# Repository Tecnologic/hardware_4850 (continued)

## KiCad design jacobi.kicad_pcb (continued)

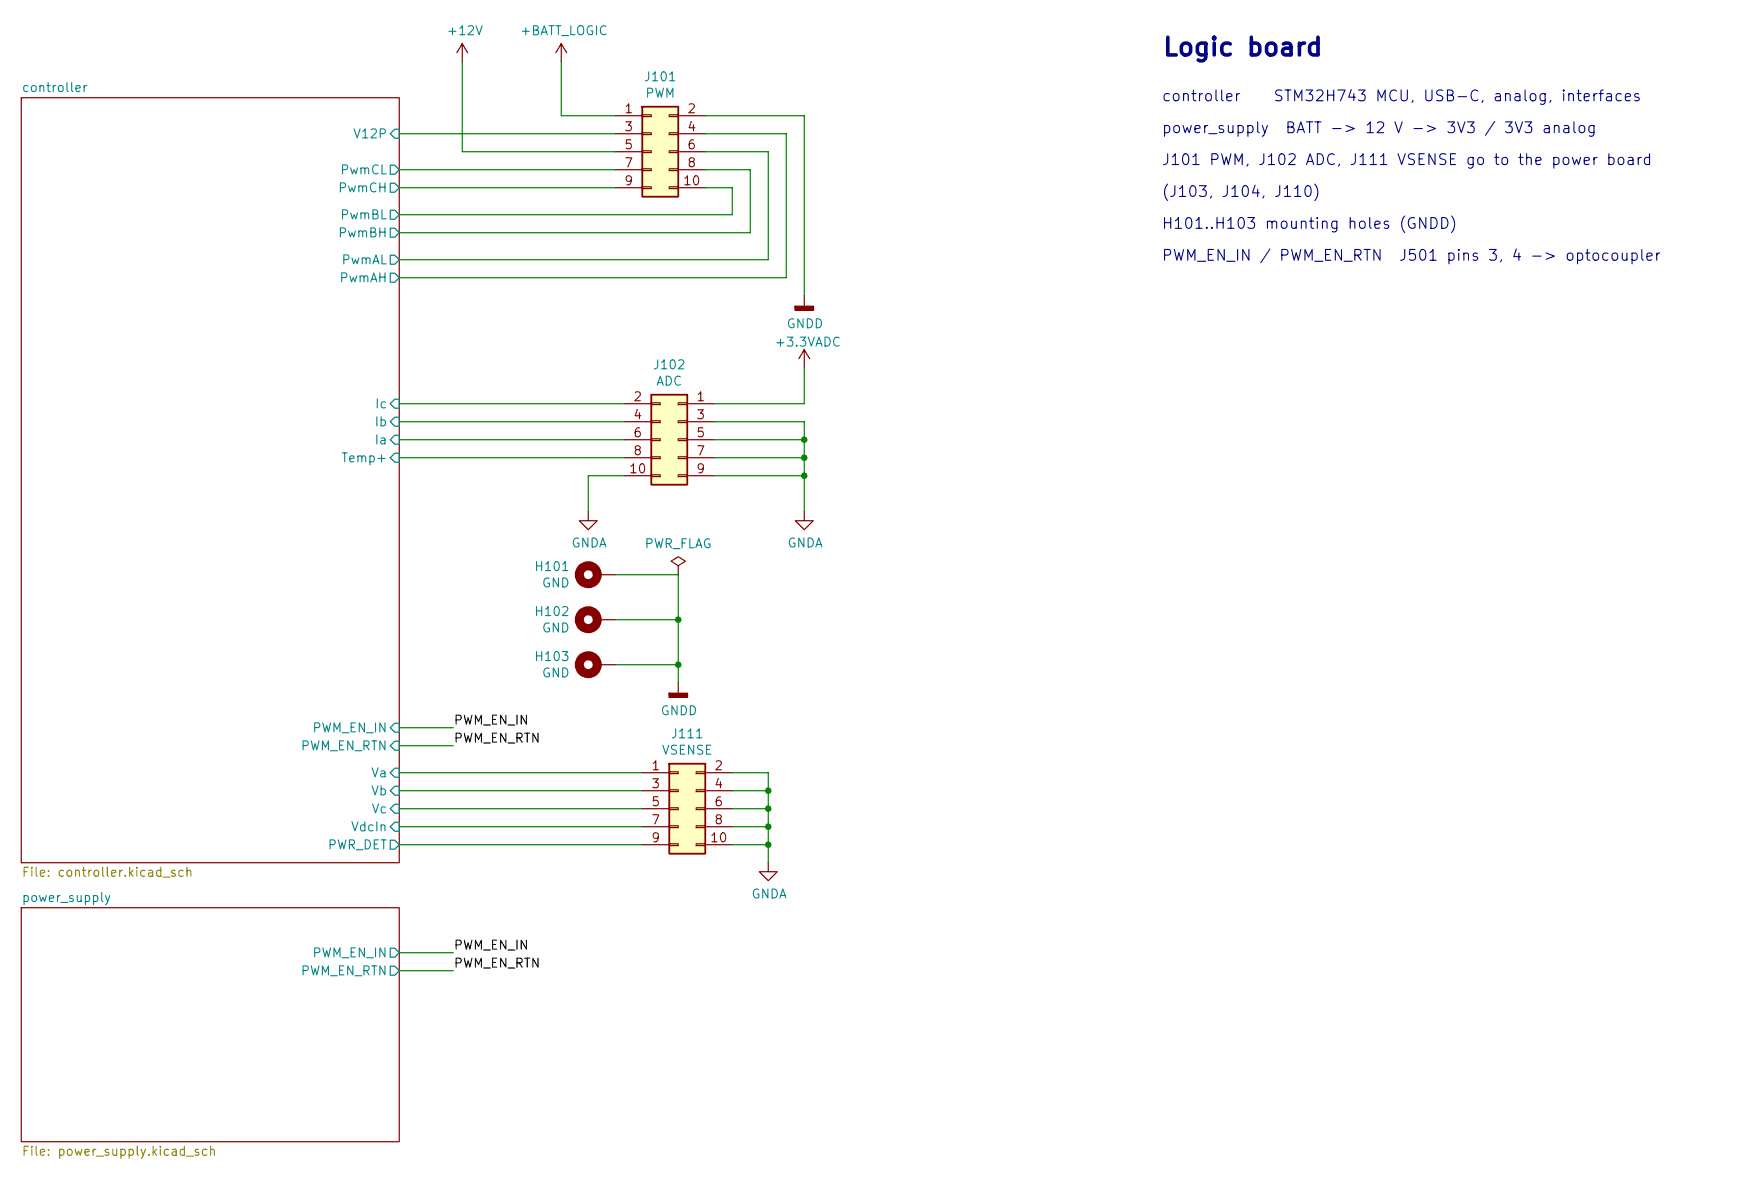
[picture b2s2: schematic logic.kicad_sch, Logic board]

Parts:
H101: GND; MountingHole_3.2mm_M3_Pad_Via
H102, H103: GND; MountingHole_3.2mm_M3_ISO14580_Pad
J101: PWM; PinHeader_2x05_P2.54mm_Vertical_SMD; Part# C124391
J102: ADC; PinHeader_2x05_P2.54mm_Vertical_SMD; Part# C124391
J111: VSENSE; PinHeader_2x05_P2.54mm_Vertical_SMD; Part# C124391

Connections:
+3.3VADC: J102.1; also elsewhere on the board
+12V: J101.5; also elsewhere on the board
+BATT_LOGIC: J101.1; also elsewhere on the board
/logic/controller/Ia: J102.6; also elsewhere on the board
/logic/controller/Ib: J102.4; also elsewhere on the board
/logic/controller/Ic: J102.2; also elsewhere on the board
/logic/controller/PWR_DET: J111.9; also elsewhere on the board
/logic/controller/PwmAH: J101.4; also elsewhere on the board
/logic/controller/PwmAL: J101.6; also elsewhere on the board
/logic/controller/PwmBH: J101.8; also elsewhere on the board
/logic/controller/PwmBL: J101.10; also elsewhere on the board
/logic/controller/PwmCH: J101.9; also elsewhere on the board
/logic/controller/PwmCL: J101.7; also elsewhere on the board
/logic/controller/Temp+: J102.8; also elsewhere on the board
/logic/controller/V12P: J101.3; also elsewhere on the board
/logic/controller/Va: J111.1; also elsewhere on the board
/logic/controller/Vb: J111.3; also elsewhere on the board
/logic/controller/Vc: J111.5; also elsewhere on the board
/logic/controller/VdcIn: J111.7; also elsewhere on the board
GNDA: J102.3, J102.5, J102.7, J102.9, J102.10, J111.2, J111.4, J111.6, J111.8, J111.10; also elsewhere on the board
GNDD: H101.1 (1_1), H102.1 (1_1), H103.1 (1_1), J101.2; also elsewhere on the board

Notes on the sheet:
power_supply BATT -> 12 V -> 3V3 / 3V3 analog
PWM_EN_IN / PWM_EN_RTN J501 pins 3, 4 -> optocoupler
(J103, J104, J110)
Logic board
J101 PWM, J102 ADC, J111 VSENSE go to the power board
controller STM32H743 MCU, USB-C, analog, interfaces
H101..H103 mounting holes (GNDD)

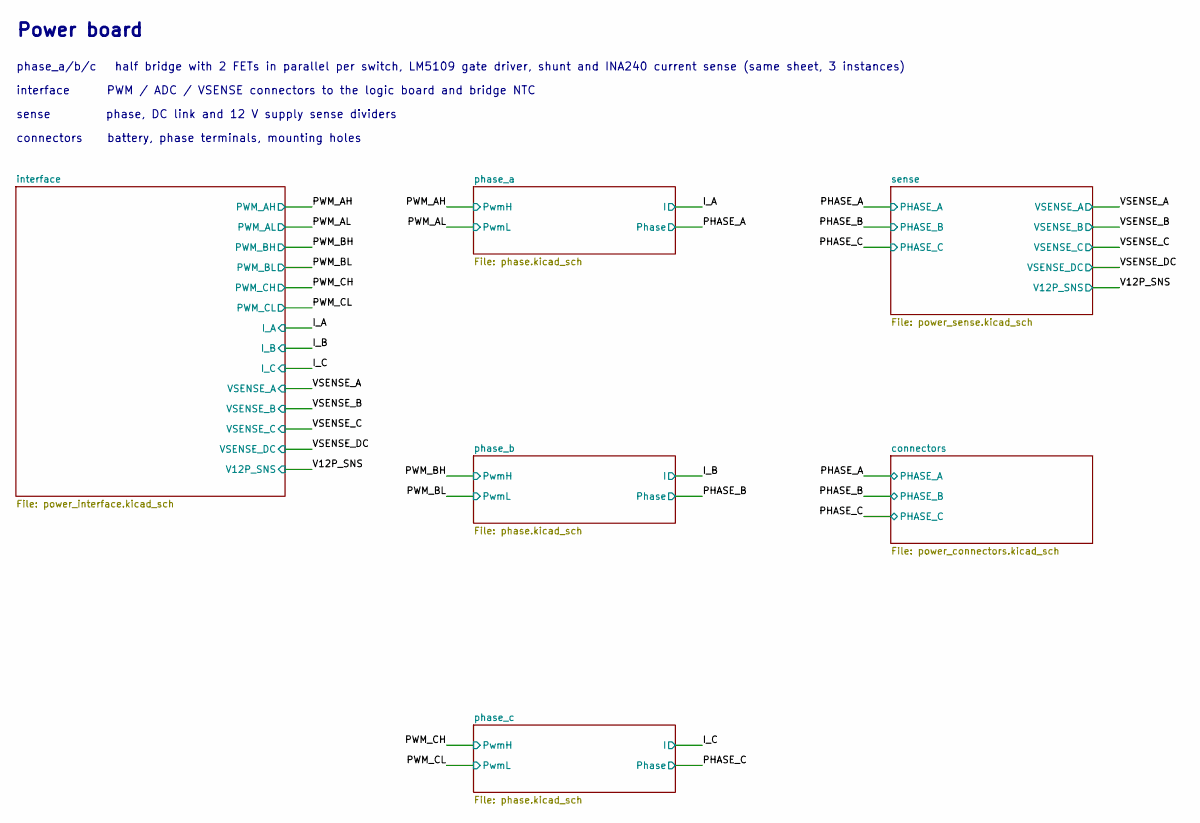
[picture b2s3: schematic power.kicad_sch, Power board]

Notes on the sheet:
phase_a/b/c half bridge with 2 FETs in parallel per switch, LM5109 gate driver, shunt and INA240 current sense (same sheet, 3 instances)
Power board
interface PWM / ADC / VSENSE connectors to the logic board and bridge NTC
sense phase, DC link and 12 V supply sense dividers
connectors battery, phase terminals, mounting holes

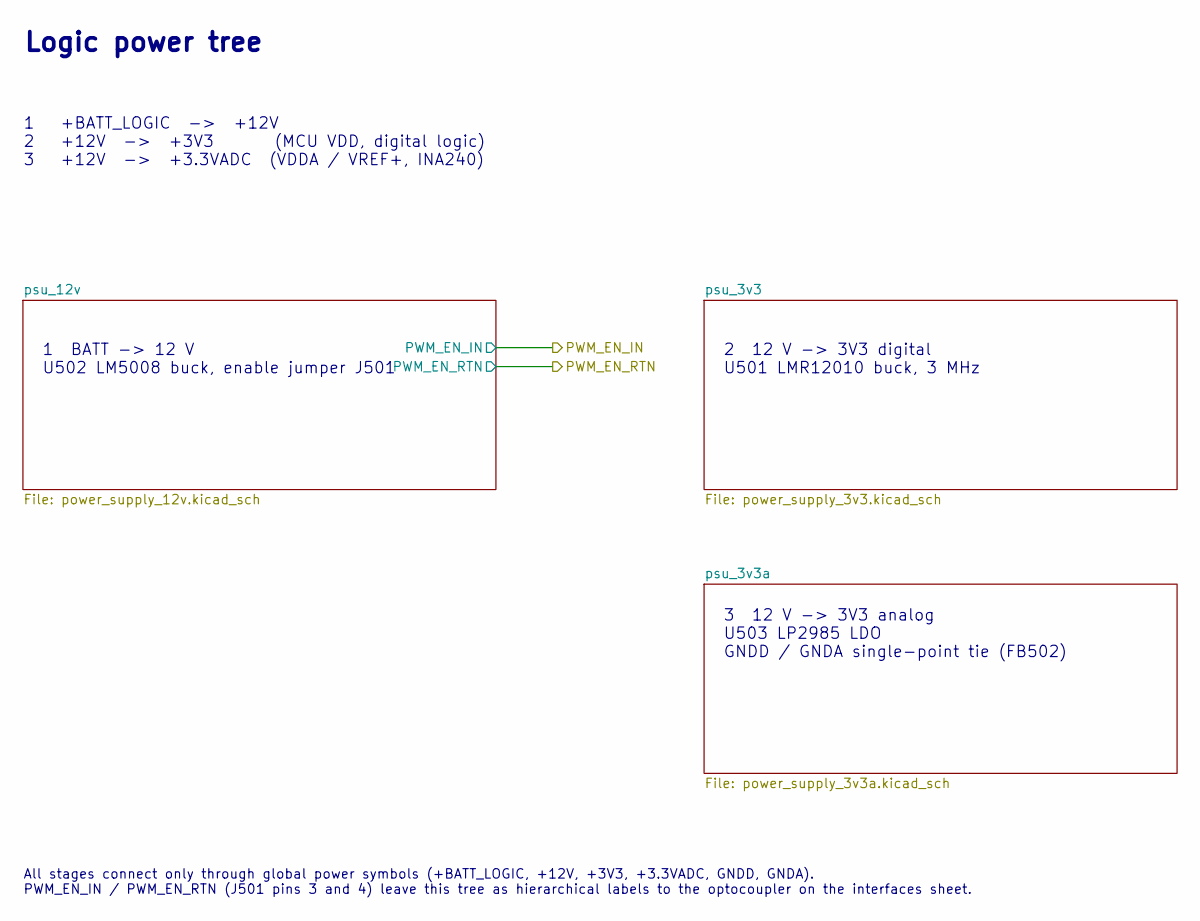
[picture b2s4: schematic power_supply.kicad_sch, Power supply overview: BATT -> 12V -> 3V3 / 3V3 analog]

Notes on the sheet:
All stages connect only through global power symbols (+BATT_LOGIC, +12V, +3V3, +3.3VADC, GNDD, GNDA). PWM_EN_IN / PWM_EN_RTN (J501 pins 3 and 4) leave this tree as hierarchical labels to the optocoupler on the interfaces sheet.
2 12 V -> 3V3 digital U501 LMR12010 buck, 3 MHz
3 12 V -> 3V3 analog U503 LP2985 LDO GNDD / GNDA single-point tie (FB502)
1 +BATT_LOGIC -> +12V 2 +12V -> +3V3 (MCU VDD, digital logic) 3 +12V -> +3.3VADC (VDDA / VREF+, INA240)
1 BATT -> 12 V U502 LM5008 buck, enable jumper J501
Logic power tree

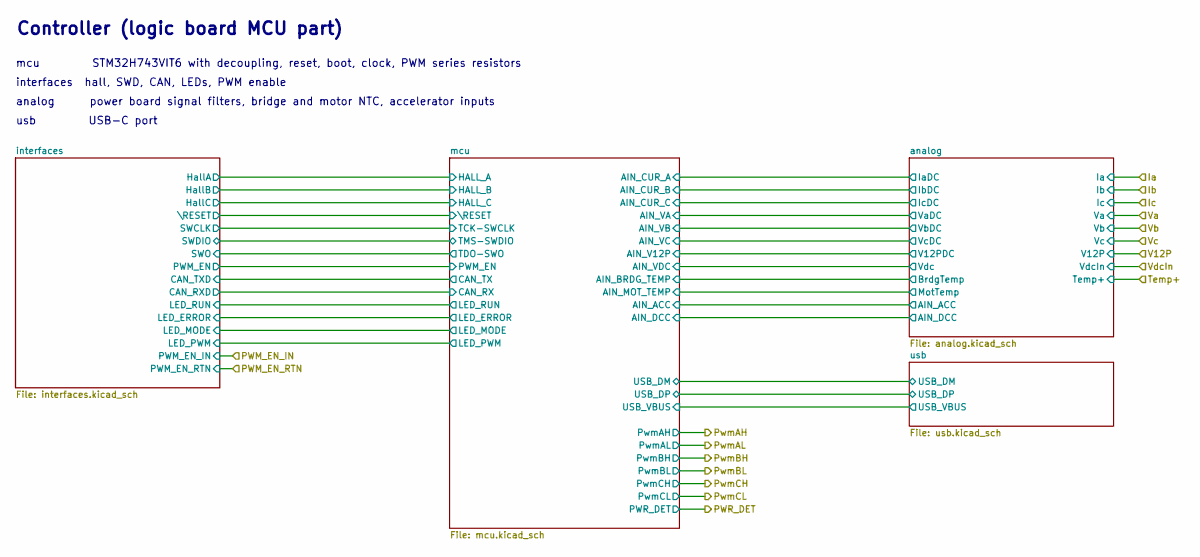
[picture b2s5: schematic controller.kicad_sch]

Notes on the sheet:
usb USB-C port
Controller (logic board MCU part)
mcu STM32H743VIT6 with decoupling, reset, boot, clock, PWM series resistors
interfaces hall, SWD, CAN, LEDs, PWM enable
analog power board signal filters, bridge and motor NTC, accelerator inputs

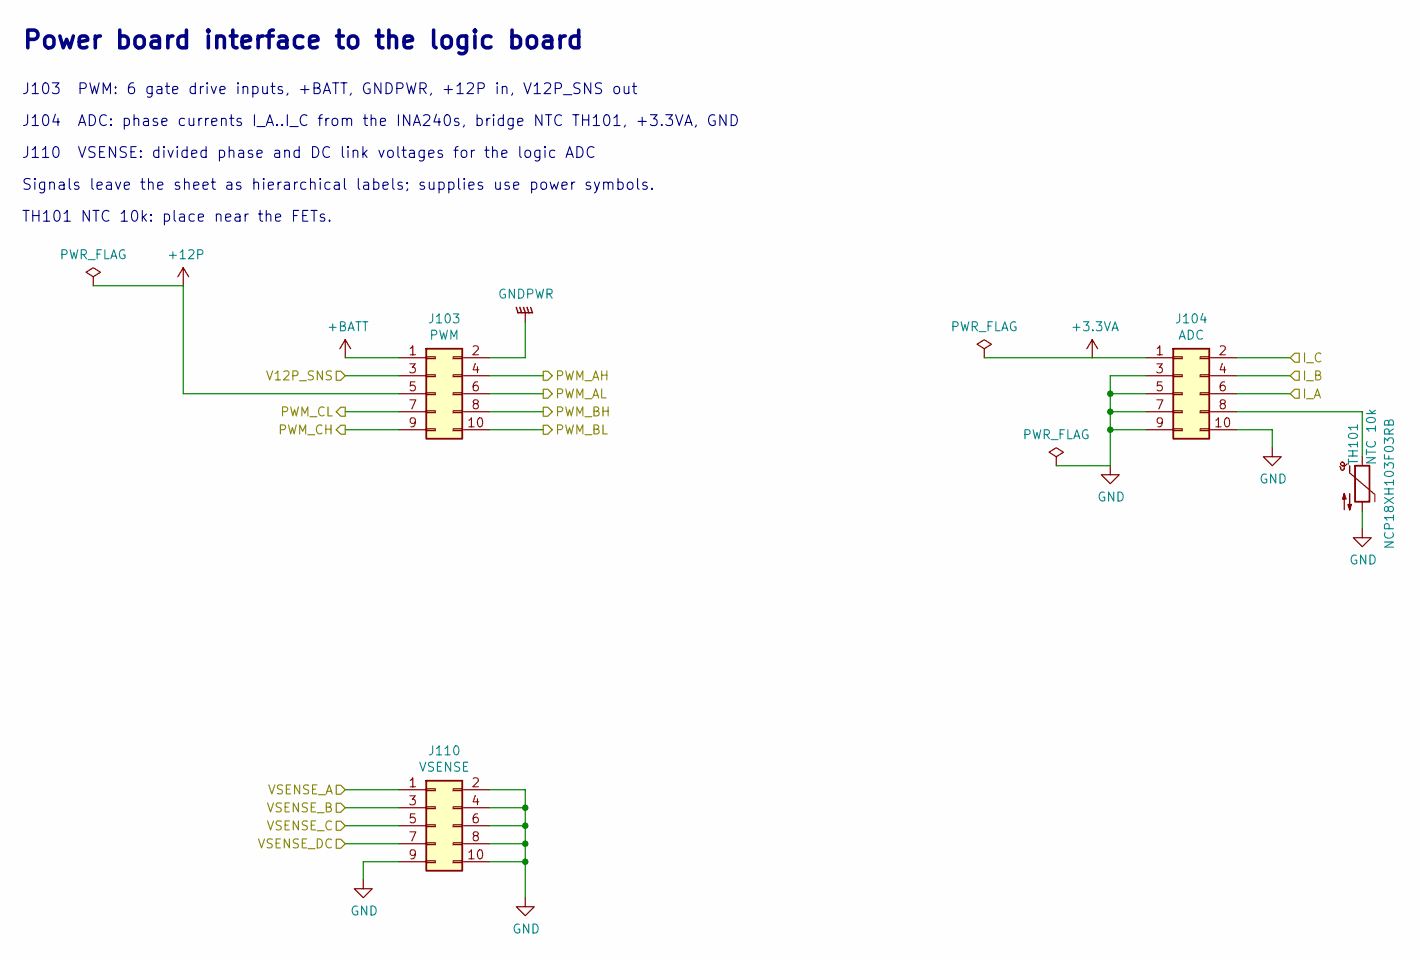
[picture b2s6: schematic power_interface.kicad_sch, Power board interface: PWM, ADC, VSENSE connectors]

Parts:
J103: PWM; PinSocket_2x05_P2.54mm_Vertical_SMD; Part# C261072
J104: ADC; PinSocket_2x05_P2.54mm_Vertical_SMD; Part# C261072
J110: VSENSE; PinSocket_2x05_P2.54mm_Vertical_SMD; Part# C261072
TH101: NTC 10k; R_0603_1608Metric; Part# NCP18XH103F03RB

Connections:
+3.3VA: J104.1; also elsewhere on the board
+12P: J103.5; also elsewhere on the board
+BATT: J103.1; also elsewhere on the board
/power/I_A: J104.6; also elsewhere on the board
/power/I_B: J104.4; also elsewhere on the board
/power/I_C: J104.2; also elsewhere on the board
/power/PWM_AH: J103.4; also elsewhere on the board
/power/PWM_AL: J103.6; also elsewhere on the board
/power/PWM_BH: J103.8; also elsewhere on the board
/power/PWM_BL: J103.10; also elsewhere on the board
/power/PWM_CH: J103.9; also elsewhere on the board
/power/PWM_CL: J103.7; also elsewhere on the board
/power/V12P_SNS: J103.3; also elsewhere on the board
/power/VSENSE_A: J110.1; also elsewhere on the board
/power/VSENSE_B: J110.3; also elsewhere on the board
/power/VSENSE_C: J110.5; also elsewhere on the board
/power/VSENSE_DC: J110.7; also elsewhere on the board
GND: J104.3, J104.5, J104.7, J104.9, J104.10, J110.2, J110.4, J110.6, J110.8, J110.9, J110.10, TH101.2; also elsewhere on the board
GNDPWR: J103.2; also elsewhere on the board
unnamed: J104.8, TH101.1

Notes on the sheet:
J110 VSENSE: divided phase and DC link voltages for the logic ADC
TH101 NTC 10k: place near the FETs.
J103 PWM: 6 gate drive inputs, +BATT, GNDPWR, +12P in, V12P_SNS out
Signals leave the sheet as hierarchical labels; supplies use power symbols.
Power board interface to the logic board
J104 ADC: phase currents I_A..I_C from the INA240s, bridge NTC TH101, +3.3VA, GND

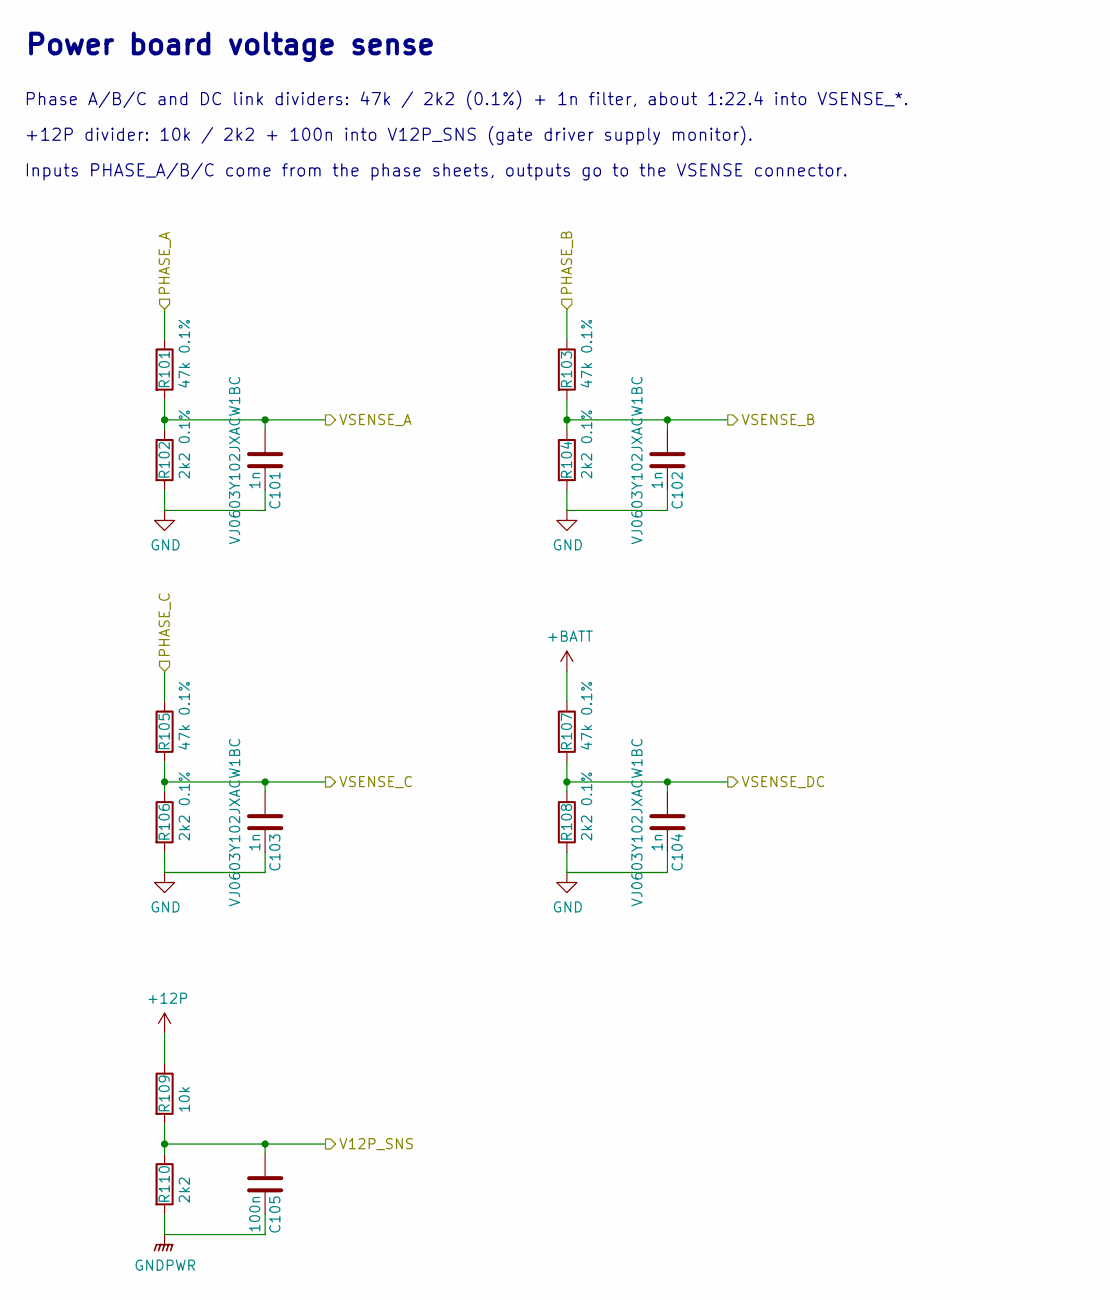
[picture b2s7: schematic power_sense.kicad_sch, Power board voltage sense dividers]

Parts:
C101, C102, C103, C104: 1n; C_0603_1608Metric; Part# VJ0603Y102JXACW1BC
C105: 100n; C_0603_1608Metric
R101, R103, R105, R107: 47k 0.1%; R_0805_2012Metric
R102, R104, R106, R108: 2k2 0.1%; R_0603_1608Metric
R109: 10k; R_0603_1608Metric
R110: 2k2; R_0603_1608Metric

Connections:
+12P: R109.1; also elsewhere on the board
+BATT: R107.1; also elsewhere on the board
/power/PHASE_A: R101.1; also elsewhere on the board
/power/PHASE_B: R103.1; also elsewhere on the board
/power/PHASE_C: R105.1; also elsewhere on the board
/power/V12P_SNS: C105.2, R109.2, R110.1; also elsewhere on the board
/power/VSENSE_A: C101.2, R101.2, R102.1; also elsewhere on the board
/power/VSENSE_B: C102.2, R103.2, R104.1; also elsewhere on the board
/power/VSENSE_C: C103.2, R105.2, R106.1; also elsewhere on the board
/power/VSENSE_DC: C104.2, R107.2, R108.1; also elsewhere on the board
GND: C101.1, C102.1, C103.1, C104.1, R102.2, R104.2, R106.2, R108.2; also elsewhere on the board
GNDPWR: C105.1, R110.2; also elsewhere on the board

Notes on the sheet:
Inputs PHASE_A/B/C come from the phase sheets, outputs go to the VSENSE connector.
+12P divider: 10k / 2k2 + 100n into V12P_SNS (gate driver supply monitor).
Power board voltage sense
Phase A/B/C and DC link dividers: 47k / 2k2 (0.1%) + 1n filter, about 1:22.4 into VSENSE_*.

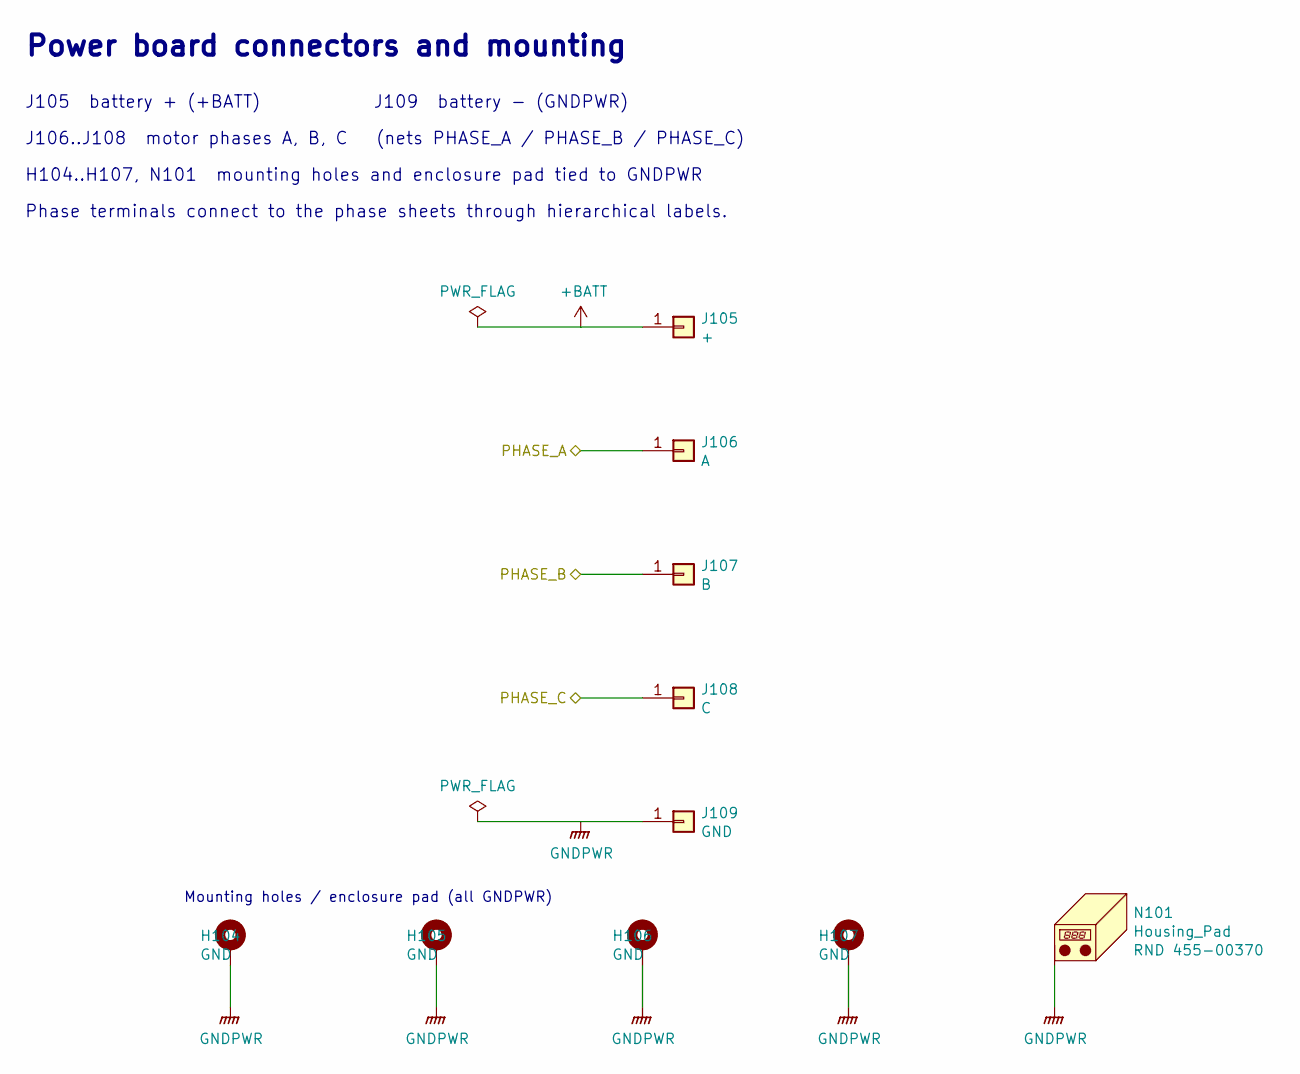
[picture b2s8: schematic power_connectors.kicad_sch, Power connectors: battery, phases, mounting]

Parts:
H104, H107: GND; MountingHole_3.2mm_M3_ISO14580_Pad
H105, H106: GND; MountingHole_3.2mm_M3_Pad_Via
J105: +; Terminal_M3_XFCN_TT34086077-0910; LCSC C19724597
J106: A; Terminal_M3_XFCN_TT34086077-0910; LCSC C19724597
J107: B; Terminal_M3_XFCN_TT34086077-0910; LCSC C19724597
J108: C; Terminal_M3_XFCN_TT34086077-0910; LCSC C19724597
J109: GND; Terminal_M3_XFCN_TT34086077-0910; LCSC C19724597
N101: Housing_Pad; RND-455-00370; Part# RND 455-00370

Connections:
+BATT: J105.1 (Pin_1_1); also elsewhere on the board
/power/PHASE_A: J106.1 (Pin_1_1); also elsewhere on the board
/power/PHASE_B: J107.1 (Pin_1_1); also elsewhere on the board
/power/PHASE_C: J108.1 (Pin_1_1); also elsewhere on the board
GNDPWR: H104.1 (1_1), H105.1 (1_1), H106.1 (1_1), H107.1 (1_1), J109.1 (Pin_1_1), N101.1 (PAD_1); also elsewhere on the board

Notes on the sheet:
J106..J108 motor phases A, B, C (nets PHASE_A / PHASE_B / PHASE_C)
Phase terminals connect to the phase sheets through hierarchical labels.
J105 battery + (+BATT) J109 battery - (GNDPWR)
Power board connectors and mounting
H104..H107, N101 mounting holes and enclosure pad tied to GNDPWR
Mounting holes / enclosure pad (all GNDPWR)

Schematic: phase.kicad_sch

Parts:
C201, C203: 10u; C_1206_3216Metric; Part# CC1206ZKY5V8BB106
C202, C205: 100n; C_0603_1608Metric; Part# CL10B104KBNC
C204: 10u; C_2220_5650Metric; Part# FS55X106K101EHG
C207, C209: 56u; CP_Elec_10x10
D201: SS110R3G; D_SMA; Part# SS110R3G
Q201, Q202, Q203, Q204: NCEP6080AG; LFPAK56_ThermalVias-1
R201: 0m5; R_Shunt_Yezhan_DSLR-5_3920_Kelvin; Part# DSLR-M-5-0.5F; LCSC C41382689
R203, R205, R207, R209: 1R1; R_0603_1608Metric
R204, R206, R208, R210: NetTie_2; NetTie-2_SMD_Pad0.5mm
R211, R212, R213, R214: 47k; R_0603_1608Metric
U201: LM5109BMA; SOIC-8_3.9x4.9mm_P1.27mm; Part# LM5109BMAX/NOPB
U202: INA240A1PWR; TSSOP-8_4.4x3mm_P0.65mm; Part# 595-INA240A1PWR

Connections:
+3.3VA: C205.1, U202.5 (V+), U202.6 (REF2); also elsewhere on the board
+12P: C201.1, C202.1, D201.2 (A), U201.1 (VDD); also elsewhere on the board
+BATT: C204.1, C207.1, C209.1, Q201.5 (D), Q203.5 (D); also elsewhere on the board
/power/I_A: U202.8; also elsewhere on the board
/power/PHASE_A: R201.1, R201.2, U202.2 (+); also elsewhere on the board
/power/PWM_AH: U201.2 (HI); also elsewhere on the board
/power/PWM_AL: U201.3 (LI); also elsewhere on the board
/power/phase_a/HO: R203.2, R209.2, U201.7 (HO)
/power/phase_a/HS: C203.2, R204.1, R210.1, U201.6 (HS)
/power/phase_a/LO: R205.2, R207.2, U201.5 (LO)
/power/phase_a/VSS: C201.2, C202.2, R206.1, R208.1, U201.4 (VSS)
GND: C205.2, U202.1 (GND), U202.4 (GND), U202.7 (REF1); also elsewhere on the board
GNDPWR: C204.2, C207.2, C209.2, Q202.1 (S), Q202.2 (S), Q202.3 (S), Q204.1 (S), Q204.2 (S), Q204.3 (S), R206.2, R208.2, R212.2, R214.2; also elsewhere on the board
unnamed: C203.1, D201.1 (K), U201.8 (HB)
unnamed: Q201.4 (G), R203.1, R211.1
unnamed: Q201.1 (S), Q201.2 (S), Q201.3 (S), Q202.5 (D), Q203.1 (S), Q203.2 (S), Q203.3 (S), Q204.5 (D), R201.4, R204.2, R210.2, R211.2, R213.2
unnamed: Q202.4 (G), R205.1, R212.1
unnamed: Q203.4 (G), R209.1, R213.1
unnamed: Q204.4 (G), R207.1, R214.1
unnamed: R201.3, U202.3 (-)

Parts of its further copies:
C301, C303, C401, C403: 10u; C_1206_3216Metric; Part# CC1206ZKY5V8BB106
C302, C305, C402, C405: 100n; C_0603_1608Metric; Part# CL10B104KBNC
C304, C404: 10u; C_2220_5650Metric; Part# FS55X106K101EHG
C307, C309, C407, C409: 56u; CP_Elec_10x10
D301, D401: SS110R3G; D_SMA; Part# SS110R3G
Q301, Q302, Q303, Q304, Q401, Q402, Q403, Q404: NCEP6080AG; LFPAK56_ThermalVias-1
R301, R401: 0m5; R_Shunt_Yezhan_DSLR-5_3920_Kelvin; Part# DSLR-M-5-0.5F; LCSC C41382689
R303, R305, R307, R309, R403, R405, R407, R409: 1R1; R_0603_1608Metric
R304, R306, R308, R310, R404, R406, R408, R410: NetTie_2; NetTie-2_SMD_Pad0.5mm
R311, R312, R313, R314, R411, R412, R413, R414: 47k; R_0603_1608Metric
U301, U401: LM5109BMA; SOIC-8_3.9x4.9mm_P1.27mm; Part# LM5109BMAX/NOPB
U302, U402: INA240A1PWR; TSSOP-8_4.4x3mm_P0.65mm; Part# 595-INA240A1PWR

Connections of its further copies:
+3.3VA: C305.1, C405.1, U302.5 (V+), U302.6 (REF2), U402.5 (V+), U402.6 (REF2); also elsewhere on the board
+12P: C301.1, C302.1, C401.1, C402.1, D301.2 (A), D401.2 (A), U301.1 (VDD), U401.1 (VDD); also elsewhere on the board
+BATT: C304.1, C307.1, C309.1, C404.1, C407.1, C409.1, Q301.5 (D), Q303.5 (D), Q401.5 (D), Q403.5 (D); also elsewhere on the board
/power/I_B: U302.8; also elsewhere on the board
/power/I_C: U402.8; also elsewhere on the board
/power/PHASE_B: R301.1, R301.2, U302.2 (+); also elsewhere on the board
/power/PHASE_C: R401.1, R401.2, U402.2 (+); also elsewhere on the board
/power/PWM_BH: U301.2 (HI); also elsewhere on the board
/power/PWM_BL: U301.3 (LI); also elsewhere on the board
/power/PWM_CH: U401.2 (HI); also elsewhere on the board
/power/PWM_CL: U401.3 (LI); also elsewhere on the board
/power/phase_b/HO: R303.2, R309.2, U301.7 (HO)
/power/phase_b/HS: C303.2, R304.1, R310.1, U301.6 (HS)
/power/phase_b/LO: R305.2, R307.2, U301.5 (LO)
/power/phase_b/VSS: C301.2, C302.2, R306.1, R308.1, U301.4 (VSS)
/power/phase_c/HO: R403.2, R409.2, U401.7 (HO)
/power/phase_c/HS: C403.2, R404.1, R410.1, U401.6 (HS)
/power/phase_c/LO: R405.2, R407.2, U401.5 (LO)
/power/phase_c/VSS: C401.2, C402.2, R406.1, R408.1, U401.4 (VSS)
GND: C305.2, C405.2, U302.1 (GND), U302.4 (GND), U302.7 (REF1), U402.1 (GND), U402.4 (GND), U402.7 (REF1); also elsewhere on the board
GNDPWR: C304.2, C307.2, C309.2, C404.2, C407.2, C409.2, Q302.1 (S), Q302.2 (S), Q302.3 (S), Q304.1 (S), Q304.2 (S), Q304.3 (S), Q402.1 (S), Q402.2 (S), Q402.3 (S), Q404.1 (S), Q404.2 (S), Q404.3 (S), R306.2, R308.2, R312.2, R314.2, R406.2, R408.2, R412.2, R414.2; also elsewhere on the board
unnamed: C303.1, D301.1 (K), U301.8 (HB)
unnamed: C403.1, D401.1 (K), U401.8 (HB)
unnamed: Q301.4 (G), R303.1, R311.1
unnamed: Q301.1 (S), Q301.2 (S), Q301.3 (S), Q302.5 (D), Q303.1 (S), Q303.2 (S), Q303.3 (S), Q304.5 (D), R301.4, R304.2, R310.2, R311.2, R313.2
unnamed: Q302.4 (G), R305.1, R312.1
unnamed: Q303.4 (G), R309.1, R313.1
unnamed: Q304.4 (G), R307.1, R314.1
unnamed: Q401.4 (G), R403.1, R411.1
unnamed: Q401.1 (S), Q401.2 (S), Q401.3 (S), Q402.5 (D), Q403.1 (S), Q403.2 (S), Q403.3 (S), Q404.5 (D), R401.4, R404.2, R410.2, R411.2, R413.2
unnamed: Q402.4 (G), R405.1, R412.1
unnamed: Q403.4 (G), R409.1, R413.1
unnamed: Q404.4 (G), R407.1, R414.1
unnamed: R301.3, U302.3 (-)
unnamed: R401.3, U402.3 (-)

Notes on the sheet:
Phase: half bridge, gate drive, current sense
R201 shunt with U202 INA240 (output I). D201 / C203 bootstrap. C204/C207/C209 DC link.
U201 LM5109 drives two FETs in parallel per switch (Q201/Q203 high, Q202/Q204 low).
Separate gate resistors per FET, R211-R214 (47k) pull each gate to its source. R204/R210 (net ties) connect HS to the high FET sources. PWM dead time: 200 ns.
R206/R208 (net ties) join the low FET sources (GNDPWR) to the driver VSS. Route VSS as a separate trace from the source pads.

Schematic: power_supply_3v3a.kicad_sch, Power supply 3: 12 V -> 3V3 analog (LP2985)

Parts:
C514, C516: 10u; C_0805_2012Metric; Part# CL21A106KAYNNNE
C515: 10n; C_0603_1608Metric; Part# CL10B103KB8NNNC
D507: BZT52C15; D_SOD-123; Part# BZT52C15
FB502: Ferrite_Bead_Small; R_0603_1608Metric; Part# ACML-0603-2000
R509: 47R; R_0805_2012Metric; Part# RC0805FR-0747RL
R510: 10k; R_0603_1608Metric; Part# MCR03ERTJ103
R511: 22k; R_0603_1608Metric; Part# MCR03ERTJ223
U503: LP2985-33DBVR; SOT-23-5; Part# LP2985-33DBVR

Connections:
+3.3VADC: C516.1, U503.5 (VOUT); also elsewhere on the board
+3V3: R510.1; also elsewhere on the board
+12V: R509.1; also elsewhere on the board
GNDA: C514.2, C515.2, C516.2, FB502.1, R511.2, U503.2 (GND); also elsewhere on the board
GNDD: D507.2 (A), FB502.2; also elsewhere on the board
unnamed: C514.1, D507.1 (K), R509.2, U503.1 (VIN)
unnamed: C515.1, U503.4 (BP)
unnamed: R510.2, R511.1, U503.3 (ON/~OFF)

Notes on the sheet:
R509 + C514: 12 V RC filter, ~340 Hz D507: clamps LP2985 input below its 16 V abs max R510/R511: LDO on at VDD ~2.0 V (2.3 V max), so VDDA < VDD + 0.3 V while VDD < 1 V (H743 DS 3.5.1) Cout >= 2.2 uF over temp: C516 here, C606 10u + C605 100n at VDDA (controller sheet)
GNDD / GNDA tie (single point)
3 12 V -> 3V3 analog (VDDA/VREF+, INA240) U503 LP2985 LDO

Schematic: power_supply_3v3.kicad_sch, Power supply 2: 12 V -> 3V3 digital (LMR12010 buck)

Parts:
C504, C508, C510: 22u; C_1210_3225Metric; Part# CL32B226MOJNNNE
C506: 100n; C_0603_1608Metric; Part# CL10B104KBNC
D502: PMLL4153; D_MiniMELF; Part# PMLL4153,115
D503: 3V3; LED_0603_1608Metric; Part# 598-8070-107F
D505: SS110R3G; D_SMA; Part# SS110R3G
L501: 4u7; L_1206_3216Metric; Part# MIP25204R7MBE
R503: 11k; R_0603_1608Metric; Part# MCR03ERTJ113
R504: 34k; R_0603_1608Metric; Part# ERJ-PA3F3402V
R507: 510R; R_0603_1608Metric; Part# MCR03ERTJ511
U501: LMR12010Y; SOT-23-6; Part# LMR12010YMK/NOPB

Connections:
+3V3: C508.1, C510.1, D502.2 (A), L501.2, R504.2, R507.2; also elsewhere on the board
+12V: C504.1, U501.4 (~SHDN), U501.5 (VIN); also elsewhere on the board
GNDD: C504.2, C508.2, C510.2, D503.1 (K), D505.2 (A), R503.1, U501.2 (GND); also elsewhere on the board
unnamed: C506.2, D502.1 (K), U501.1 (CB)
unnamed: D503.2 (A), R507.1
unnamed: C506.1, D505.1 (K), L501.1, U501.6 (SW)
unnamed: R503.2, R504.1, U501.3 (FB)

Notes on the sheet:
2 12 V -> 3V3 digital U501 LMR12010 buck, 3 MHz

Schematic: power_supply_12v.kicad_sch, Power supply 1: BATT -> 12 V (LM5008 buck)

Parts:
C501: 10u; C_2220_5650Metric; Part# FS55X106K101EHG
C502, C503, C507: 100n; C_0603_1608Metric; Part# CL10B104KBNC
C505: 1u; C_0603_1608Metric; Part# CL10B105KANC
C509, C513: 4n7; C_0603_1608Metric; Part# GRM1885C1H472JA01D
C511: 22u; C_1210_3225Metric; Part# CL32B226MOJNNNE
D501: SS110R3G; D_SMA; Part# SS110R3G
D504: 12V; LED_0603_1608Metric; Part# 598-8070-107F
D506: PMLL4153; D_MiniMELF; Part# PMLL4153,115
J501: Enable; JST_PH_S4B-PH-K_1x04_P2.00mm_Horizontal; Part# C157926
L502: 330u; L_Taiyo-Yuden_NR-80xx_HandSoldering; Part# SMNR8040-331MT
R501: 220k; R_0603_1608Metric; Part# CR0603JA0224G
R502: 100k; R_0603_1608Metric; Part# CR0603-JW-104ELF
R505: 11k; R_0603_1608Metric; Part# MCR03ERTJ113
R506: 2k7; R_0603_1608Metric; Part# RS-03K272JT
R508: 100k; R_0603_1608Metric; Part# MCR03ERTJ104
R513: 3k3; R_0603_1608Metric
U502: LM5008; MSOP-8_3x3mm_P0.65mm; Part# LM5008MMX/NOPB

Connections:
+12V: C511.1, C513.1, D506.2 (A), L502.2, R505.2, R513.1; also elsewhere on the board
+BATT_LOGIC: J501.1; also elsewhere on the board
/logic/PWM_EN_IN: J501.3; also elsewhere on the board
/logic/PWM_EN_RTN: J501.4; also elsewhere on the board
GNDD: C501.2, C503.2, C505.1, C511.2, D501.2 (A), D504.1 (K), R502.1, R506.1, U502.4 (RTN); also elsewhere on the board
unnamed: C502.2, C503.1
unnamed: C509.1, C513.2, R508.2
unnamed: C507.1, D501.1 (K), L502.1, R508.1, U502.1 (SW)
unnamed: D504.2 (A), R513.2
unnamed: C505.2, D506.1 (K), U502.7 (VCC)
unnamed: C501.1, C502.1, J501.2, R501.2, U502.8 (VIN)
unnamed: C507.2, U502.2 (BST)
unnamed: C509.2, R505.1, R506.2, U502.5 (FB)
unnamed: R502.2, U502.3 (RCL)
unnamed: R501.1, U502.6 (RON/SD)

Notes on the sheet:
Ripple injection (LM5008 needs >=25mV at FB): Rr=R508 / Cr=C513 across L502, Cac=C509 into FB ~45mV @ 36V in, ~50mV @ 60V in
J501 Enable / supply input
1 +BATT_LOGIC battery + 2 buck VIN (U502 LM5008) 3 PWM_EN_IN, optocoupler U1102 input + (12 - 40 V) 4 PWM_EN_RTN, optocoupler input return, battery - (floating, not GNDD) Bench: bridge 1-2, battery + to pin 3, battery - to pin 4. Cart: switch pin 2 (logic), pin 3 (phases).
1 BATT -> 12 V U502 LM5008 buck

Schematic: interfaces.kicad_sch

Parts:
C1101, C1102, C1103, C1104: 100n; C_0603_1608Metric; Part# CL10B104KBNC
C1106, C1107: 1u; C_0603_1608Metric; Part# CL10B105KANC
C1108, C1109: 10n; C_0603_1608Metric; Part# CL10B103KB8NNNC
D1101: RUN; LED_0603_1608Metric; Part# 598-8070-107F
D1102: ERROR; LED_0603_1608Metric; Part# 598-8070-107F
D1103: FW; LED_0603_1608Metric; Part# 598-8070-107F
D1104: PWM; LED_0603_1608Metric; Part# 598-8070-107F
D1105: 1N4148W; D_SOD-123; Part# 1N4148W
J1101: HALL; JST_PH_S5B-PH-K_1x05_P2.00mm_Horizontal; Part# C157923
J1103: CAN_IN; JST_PH_S4B-PH-K_1x04_P2.00mm_Horizontal; Part# C157926
J1104: CAN_Out; JST_PH_S4B-PH-K_1x04_P2.00mm_Horizontal; Part# C157926
P1101: SWD; PinHeader_2x05_P1.27mm_Vertical
R1101, R1102, R1103, R1104, R1105, R1106, R1107, R1110, R1111: 510R; R_0603_1608Metric; Part# MCR03ERTJ511
R1108, R1109, R1114: 11R; R_0603_1608Metric; Part# MCR03ERTJ11R
R1115: 10k; R_1206_3216Metric; Part# MCR18EZPJ103
R1116: 10k; R_0603_1608Metric; Part# MCR03ERTJ103
U1101: TCAN334; SOT-23-8; Part# TCAN334DCNR
U1102: TLP291; SOIC-4_4.55x2.6mm_P1.27mm; Part# TLP291
U1103: AP2204K-5.0; SOT-23-5

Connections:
+3V3: C1104.1, P1101.1, R1105.2, U1101.3 (VCC); also elsewhere on the board
+12V: C1107.1, U1103.1 (VIN), U1103.3 (EN); also elsewhere on the board
/logic/PWM_EN_IN: R1115.1; also elsewhere on the board
/logic/PWM_EN_RTN: C1108.2, D1105.2 (A), U1102.2; also elsewhere on the board
/logic/controller/interfaces/CAN_RXD: R1109.2; also elsewhere on the board
/logic/controller/interfaces/CAN_TXD: R1108.2; also elsewhere on the board
/logic/controller/interfaces/HallA: C1101.1, R1104.1; also elsewhere on the board
/logic/controller/interfaces/HallB: C1102.1, R1103.1; also elsewhere on the board
/logic/controller/interfaces/HallC: C1103.1, R1102.1; also elsewhere on the board
/logic/controller/interfaces/LED_ERROR: R1107.2; also elsewhere on the board
/logic/controller/interfaces/LED_MODE: R1110.2; also elsewhere on the board
/logic/controller/interfaces/LED_PWM: R1111.2; also elsewhere on the board
/logic/controller/interfaces/LED_RUN: R1106.2; also elsewhere on the board
/logic/controller/interfaces/PWM_EN: R1101.2; also elsewhere on the board
/logic/controller/interfaces/SWCLK: P1101.4; also elsewhere on the board
/logic/controller/interfaces/SWDIO: P1101.2; also elsewhere on the board
/logic/controller/interfaces/SWO: P1101.6; also elsewhere on the board
/logic/controller/mcu/\RESET: P1101.10; also elsewhere on the board
GNDD: C1101.2, C1102.2, C1103.2, C1104.2, C1106.2, C1107.2, C1109.2, D1101.1 (K), D1102.1 (K), D1103.1 (K), D1104.1 (K), J1101.1, P1101.3, P1101.5, R1114.2, R1116.2, U1101.2 (GND), U1103.2 (GND); also elsewhere on the board
unnamed: C1109.1, R1101.1, R1116.1, U1102.3
unnamed: D1101.2 (A), R1106.1
unnamed: D1102.2 (A), R1107.1
unnamed: D1103.2 (A), R1110.1
unnamed: D1104.2 (A), R1111.1
unnamed: C1108.1, D1105.1 (K), R1115.2, U1102.1
unnamed: J1101.2, R1104.2
unnamed: J1101.3, R1103.2
unnamed: J1101.4, R1102.2
unnamed: C1106.1, J1101.5, U1103.5 (VOUT)
unnamed: J1103.1, J1104.1, R1114.1
unnamed: J1103.2, J1104.2, U1101.6 (CANL)
unnamed: J1103.3, J1104.3, U1101.7 (CANH)
unnamed: J1103.4, J1104.4
unnamed: R1105.1, U1102.4
unnamed: R1109.1, U1101.4 (RXD)
unnamed: R1108.1, U1101.1 (TXD)

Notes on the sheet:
SWD-Interface 10-Pin ARM connector
LED: 10k + 10n RC filter, 1 - 4 mA at 12 - 40 V, 1N4148W against reverse polarity. LED return is PWM_EN_RTN (J501 pin 4), floating: keep it off GNDD. Output: collector to +3V3 via 510R, emitter pulls PE15 high. 10k pulldown + 10n hold PE15 low when off and filter noise.
PWM_EN input (optocoupler U1102 TLP291)

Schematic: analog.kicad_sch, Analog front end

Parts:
C602, C604, C701, C709: 100n; C_0603_1608Metric; Part# CL10B104KBNC
C703, C704, C719: 10n; C_0603_1608Metric
C713, C714, C715, C716, C717, C718: 2n2; C_0603_1608Metric
J601: AIN; JST_PH_S4B-PH-K_1x04_P2.00mm_Horizontal; Part# C157926
J701: MOT_TEMP; JST_PH_S2B-PH-K_1x02_P2.00mm_Horizontal; Part# C157929
R602, R603: 11k; R_0603_1608Metric; Part# MCR03ERTJ113
R703, R716: 10k 0.1%; R_0603_1608Metric; Part# ARG03BTC1002
R704, R705: 4k7; R_0603_1608Metric; Part# 0603WAJ0472T5E
R717, R718, R719, R720, R721, R722: 220R; R_0603_1608Metric
R723: 4k7; R_0603_1608Metric

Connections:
+3.3VADC: J601.4, R703.2, R716.2; also elsewhere on the board
/logic/controller/Ia: R717.2; also elsewhere on the board
/logic/controller/Ib: R718.2; also elsewhere on the board
/logic/controller/Ic: R719.2; also elsewhere on the board
/logic/controller/Temp+: C701.1, R703.1, R704.2; also elsewhere on the board
/logic/controller/V12P: R723.2; also elsewhere on the board
/logic/controller/Va: R720.2; also elsewhere on the board
/logic/controller/Vb: R721.2; also elsewhere on the board
/logic/controller/Vc: R722.2; also elsewhere on the board
/logic/controller/VdcIn: R705.2; also elsewhere on the board
/logic/controller/analog/AIN_ACC: C602.1, R602.2; also elsewhere on the board
/logic/controller/analog/AIN_DCC: C604.1, R603.2; also elsewhere on the board
/logic/controller/analog/BrdgTemp: C703.2, R704.1; also elsewhere on the board
/logic/controller/analog/IaDC: C713.2, R717.1; also elsewhere on the board
/logic/controller/analog/IbDC: C714.2, R718.1; also elsewhere on the board
/logic/controller/analog/IcDC: C715.2, R719.1; also elsewhere on the board
/logic/controller/analog/MotTemp: C709.1, J701.2, R716.1; also elsewhere on the board
/logic/controller/analog/V12PDC: C719.2, R723.1; also elsewhere on the board
/logic/controller/analog/VaDC: C716.2, R720.1; also elsewhere on the board
/logic/controller/analog/VbDC: C717.2, R721.1; also elsewhere on the board
/logic/controller/analog/VcDC: C718.2, R722.1; also elsewhere on the board
/logic/controller/mcu/AIN_VDC: C704.2, R705.1; also elsewhere on the board
GNDA: C602.2, C604.2, C701.2, C703.1, C704.1, C709.2, C713.1, C714.1, C715.1, C716.1, C717.1, C718.1, C719.1, J601.1, J701.1; also elsewhere on the board
unnamed: J601.2, R603.1
unnamed: J601.3, R602.1

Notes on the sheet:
RC filters: phase currents Ia..Ic, phase voltages Va..Vc,
DC link voltage and 12 V sense into the MCU ADC
Accelerator input J601 (AIN_ACC / AIN_DCC)
All filters reference GNDA
Analog front end
Bridge NTC (Temp+) and motor NTC (J701): 3.3VADC pull-ups

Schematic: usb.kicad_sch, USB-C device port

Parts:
J602: TYPE-C-31-M-12; USB_C_Receptacle_HRO_TYPE-C-31-M-12; LCSC C165948
R604: 4k7; R_0603_1608Metric; Part# 0603WAJ0472T5E
R605: 11k; R_0603_1608Metric; Part# MCR03ERTJ113
R613, R614: 5k1; R_0603_1608Metric; Part# MCR03ERTJ512

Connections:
/logic/controller/mcu/USB_DM: J602.A7 (D-), J602.B7 (D-); also elsewhere on the board
/logic/controller/mcu/USB_DP: J602.A6 (D+), J602.B6 (D+); also elsewhere on the board
/logic/controller/mcu/USB_VBUS: R604.2, R605.2; also elsewhere on the board
/logic/controller/usb/VBUS: J602.A4 (VBUS), J602.A9 (VBUS), J602.B4 (VBUS), J602.B9 (VBUS), R604.1
GNDD: J602.A1 (GND), J602.A12 (GND), J602.B1 (GND), J602.B12 (GND), J602.SH (SHIELD), R605.1, R613.1, R614.1; also elsewhere on the board
unnamed: J602.A5 (CC1), R613.2
unnamed: J602.B5 (CC2), R614.2

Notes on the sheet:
USB-C device port (FS), VBUS sense
